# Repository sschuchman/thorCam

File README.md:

# Thoracic Camera

## Overview
The **Thoracic Camera** project is a collaborative effort to design a dynamic thoracic camera system capable of precision actuation and real-time feedback for use in minimally invasive surgeries. By combining a Raspberry Pi 5 for advanced processing and a Raspberry Pi Pico for motor control and sensor feedback, the system delivers a robust solution for camera tracking and actuation in the chest cavity.

---

## Contributors
- **Sean Schuchman**: January 2024 - December 2024  
- **Jakob Schoeberle**: August 2024 - December 2024  
- **Colton Wall**: August 2024 - December 2024  

---

## Hardware

### Raspberry Pi 5
- **Role**: Central processing hub for the system.  
- **Responsibilities**:
  - Handles video feed from the Pi Camera Module V3.
  - Performs computer vision tasks to detect and track a target object.
  - Sends actuation commands to the Pico Controller via UART.

### Pico Controller (Raspberry Pi Pico)
- **Role**: Camera actuation controller.  
- **Responsibilities**:
  - Interprets movement commands from the Raspberry Pi 5 and drives stepper motors.
  - Monitors sensor feedback from tension modules to ensure proper wire tension.
  - Handles precise actuation of the thoracic camera in response to commands.

---

## Pico Controller
The **Pico Controller** acts as an abstraction layer between the computer vision system on the Raspberry Pi 5 and the physical camera actuation system. It simplifies control by encapsulating motor and tension management, providing an easy-to-interface control system.  

### Features:
- **Camera Actuation**:  
  Controls stepper motors to manipulate tension wires, enabling the camera to move along the x-plane and y-plane directions.  
- **Tension Monitoring**:  
  Uses sensor feedback from load cells to dynamically adjust wires and maintain system balance.  
- **Control Modes**:  
  - **Manual Mode**: Direct input to move the camera.  
  - **Automatic Mode**: Actuation based on computer vision commands from the Raspberry Pi 5.  

---

## Directory Structure
The project is divided into several directories to organize hardware, software, and firmware resources.

- `/Software`: Contains software running on the Raspberry Pi 5, including computer vision and the Flask web application for control.  
- `/Firmware`: Firmware for the Raspberry Pi Pico to manage motor control and tension monitoring.  
- `/Hardware`: Schematic diagrams, PCB designs, and other hardware resources.  
- `/Datasheets`: Documentation for components such as stepper motors, motor drivers, and sensors.  
- `/3D_Models`: 3D printable designs for physical components.  
- `/legacy`: Archive of previous iterations or deprecated designs.

---

## Setup

### Raspberry Pi Pico Setup
1. **Development Environment**:
   - Use Visual Studio Code with the Raspberry Pi Pico extension to build and flash the firmware.
   - Ensure the Raspberry Pi Pico Debug Probe is connected for flashing and debugging.  

2. **Firmware Installation**:
   - Clone the repository and navigate to the `/Firmware` directory.
   - Open the project in Visual Studio Code and use the Pico extension to compile and flash the firmware.  

3. **Hardware Connections**:
   - Connect stepper motors via L293D drivers to the GPIO pins.
   - Connect ADS1115 ADC modules to GPIO4 (SDA) and GPIO5 (SCL).
   - Ensure UART pins (GPIO0 and GPIO1) are connected to the Raspberry Pi 5 for communication.

### Raspberry Pi 5 Setup
1. **Install Required Software**:
   - Ensure Python is installed with the required libraries (`Flask`, `OpenCV`, etc.).
   - Navigate to the `/Software` directory and install dependencies using:
     ```bash
     pip install -r requirements.txt
     ```

2. **Start the Web Application**:
   - Run the `app.py` script to start the Flask web server:
     ```bash
     python app.py
     ```
   - Access the control interface via a web browser on the local network.

3. **Hardware Connections**:
   - Connect the Pi Camera Module V3 to the CSI port.
   - Ensure UART is configured on `/dev/ttyAMA0` for communication with the Pico Controller.

---

## Usage
1. **Manual Control**:
   - Use the web interface to manually send movement commands to the Pico Controller.
   - Adjust camera settings and monitor sensor feedback through the interface.

2. **Automatic Control**:
   - Enable automatic mode via the web interface to allow the system to track a selected object.
   - The Raspberry Pi 5 processes the video feed to calculate the offset and sends movement commands to the Pico Controller.

3. **Real-Time Feedback**:
   - Monitor sensor values and system logs in the web interface.
   - View live video and mask feeds to verify object tracking.

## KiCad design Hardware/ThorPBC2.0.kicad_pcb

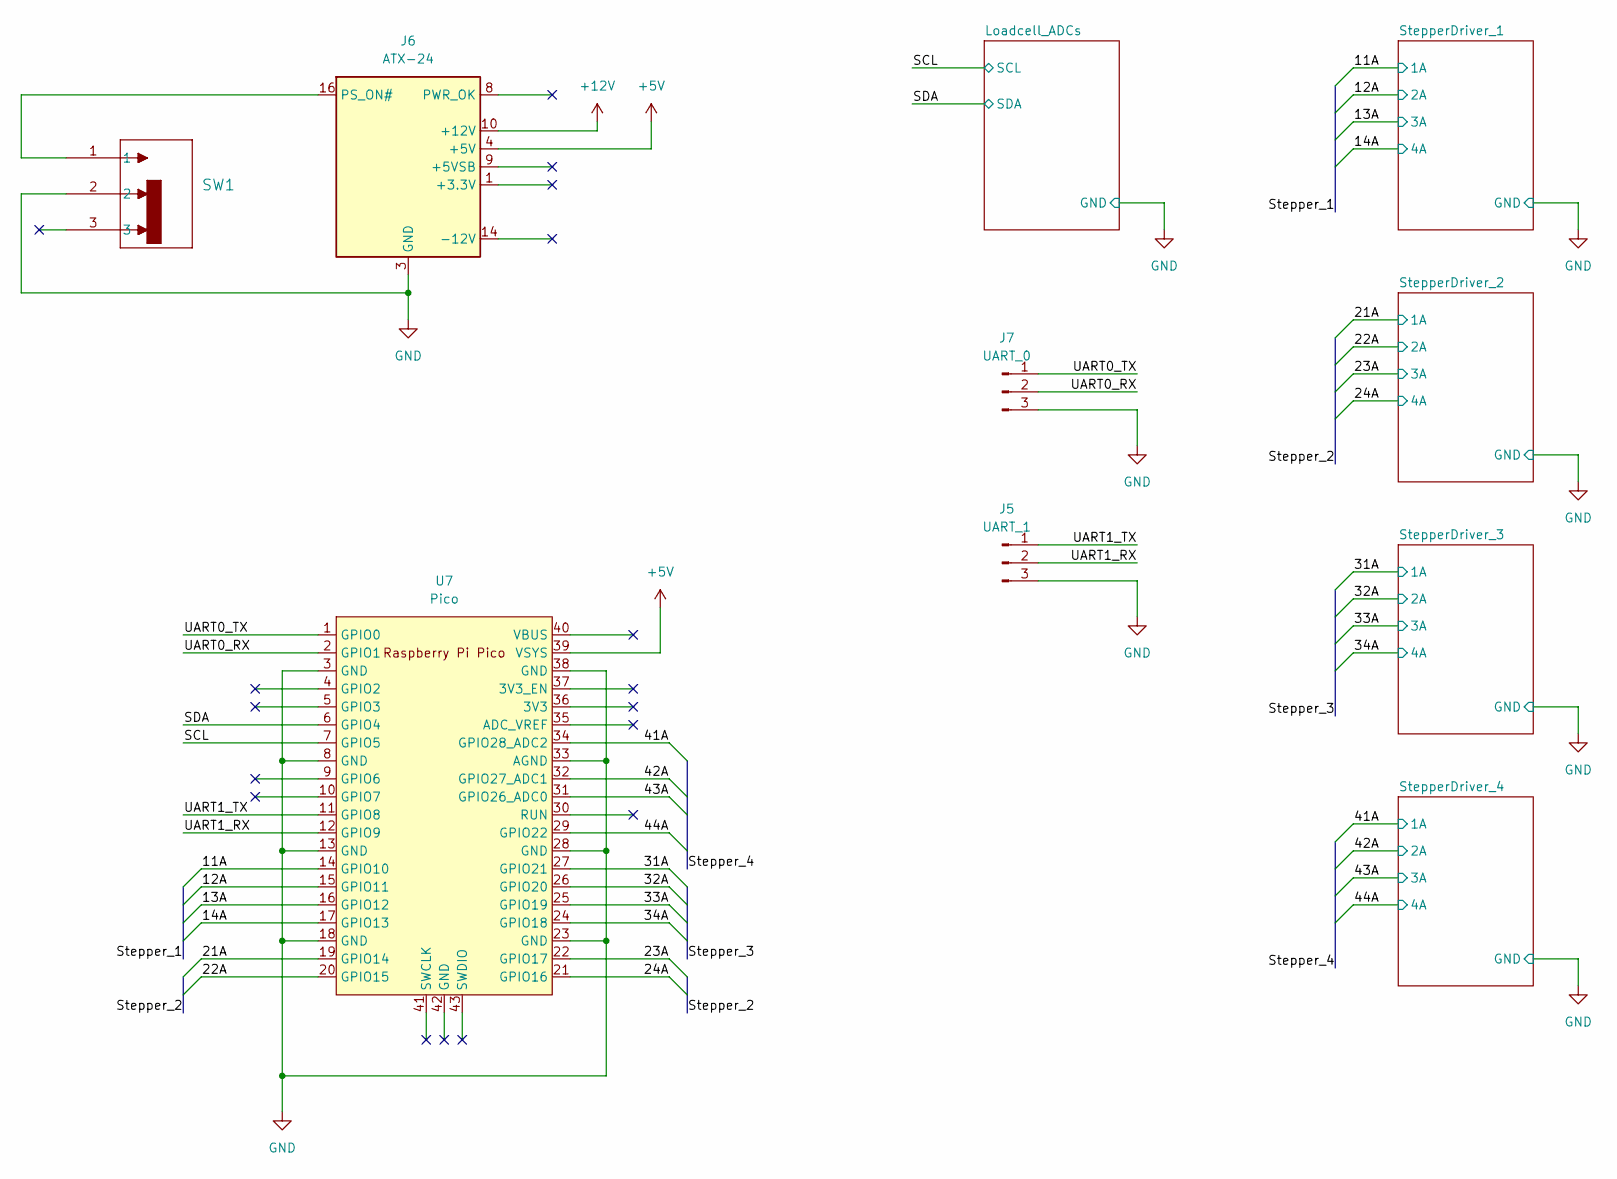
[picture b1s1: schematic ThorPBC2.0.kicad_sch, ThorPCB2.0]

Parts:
J5: UART_1; PinHeader_1x03_P2.54mm_Vertical
J6: ATX-24; Molex_Mini-Fit_Jr_5566-24A_2x12_P4.20mm_Vertical_Thor
J7: UART_0; PinHeader_1x03_P2.54mm_Vertical
SW1: OS102011MS2QN1; SPDT_OS102011_CNK
U7: Pico; RPi_Pico_SMD_TH

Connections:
+5V: J6.4 (+5V), J6.6 (+5V), J6.21 (+5V), J6.22 (+5V), J6.23 (+5V), U7.39 (VSYS); also elsewhere on the board
+12V: J6.10 (+12V), J6.11 (+12V); also elsewhere on the board
/11A: U7.14 (GPIO10); also elsewhere on the board
/12A: U7.15 (GPIO11); also elsewhere on the board
/13A: U7.16 (GPIO12); also elsewhere on the board
/14A: U7.17 (GPIO13); also elsewhere on the board
/21A: U7.19 (GPIO14); also elsewhere on the board
/22A: U7.20 (GPIO15); also elsewhere on the board
/23A: U7.22 (GPIO17); also elsewhere on the board
/24A: U7.21 (GPIO16); also elsewhere on the board
/31A: U7.27 (GPIO21); also elsewhere on the board
/32A: U7.26 (GPIO20); also elsewhere on the board
/33A: U7.25 (GPIO19); also elsewhere on the board
/34A: U7.24 (GPIO18); also elsewhere on the board
/41A: U7.34 (GPIO28_ADC2); also elsewhere on the board
/42A: U7.32 (GPIO27_ADC1); also elsewhere on the board
/43A: U7.31 (GPIO26_ADC0); also elsewhere on the board
/44A: U7.29 (GPIO22); also elsewhere on the board
/SCL: U7.7 (GPIO5); also elsewhere on the board
/SDA: U7.6 (GPIO4); also elsewhere on the board
/UART0_RX: J7.2, U7.2 (GPIO1)
/UART0_TX: J7.1, U7.1 (GPIO0)
/UART1_RX: J5.2, U7.12 (GPIO9)
/UART1_TX: J5.1, U7.11 (GPIO8)
GND: J5.3, J6.3 (GND), J6.5 (GND), J6.7 (GND), J6.15 (GND), J6.17 (GND), J6.18 (GND), J6.19 (GND), J6.24 (GND), J7.3, SW1.2, U7.3 (GND), U7.8 (GND), U7.13 (GND), U7.18 (GND), U7.23 (GND), U7.28 (GND), U7.33 (AGND), U7.38 (GND); also elsewhere on the board
unnamed: J6.16 (PS_ON#), SW1.1

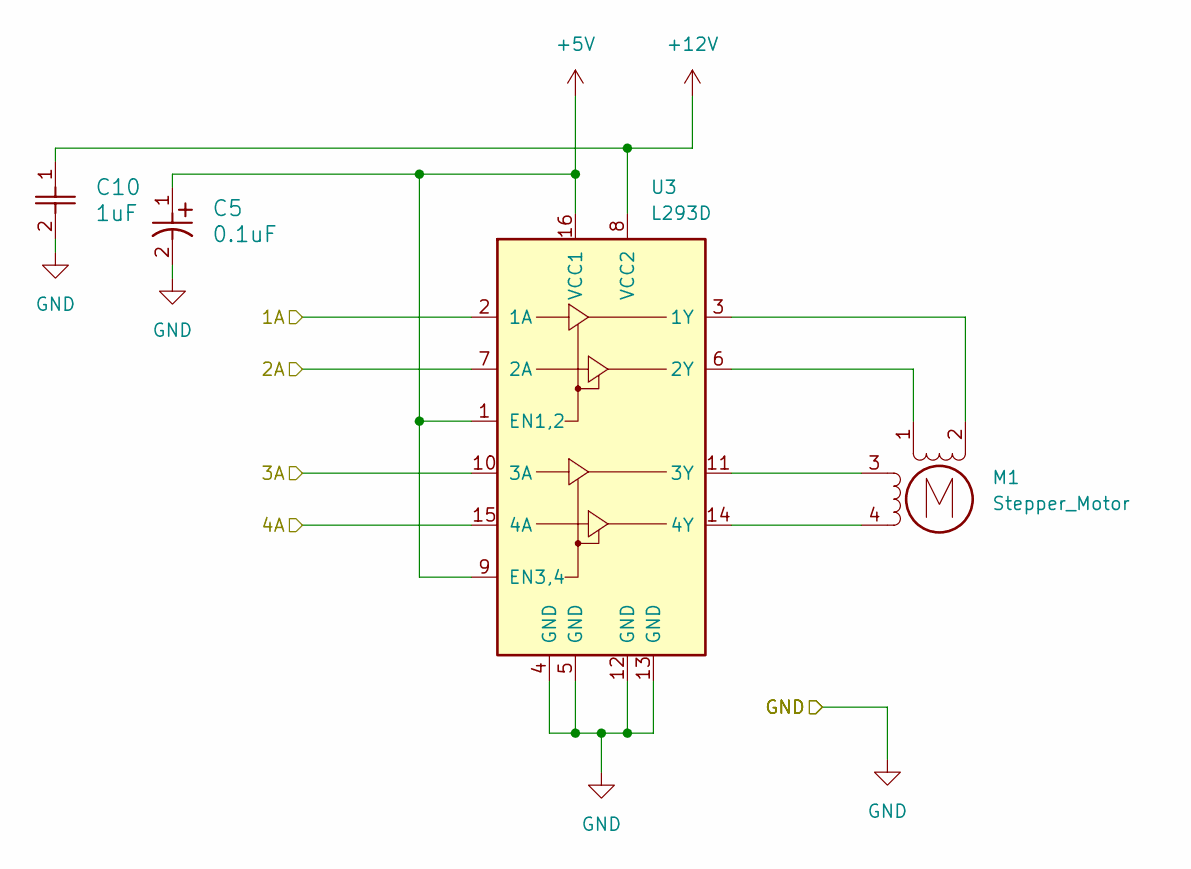
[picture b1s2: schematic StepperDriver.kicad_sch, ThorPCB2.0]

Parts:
C5: 0.1uF; CAP_C320_KEM
C10: 1uF; CAP_C330C_MR_X7R_KEM
M1: Stepper_Motor; TerminalBlock_Phoenix_MPT-0,5-4-2.54_1x04_P2.54mm_Horizontal
U3: L293D; DIP-16_W7.62mm

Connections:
+5V: C5.1, U3.1 (EN1,2), U3.9 (EN3,4), U3.16 (VCC1); also elsewhere on the board
+12V: C10.1, U3.8 (VCC2); also elsewhere on the board
/11A: U3.2 (1A); also elsewhere on the board
/12A: U3.7 (2A); also elsewhere on the board
/13A: U3.10 (3A); also elsewhere on the board
/14A: U3.15 (4A); also elsewhere on the board
GND: C5.2, C10.2, U3.4 (GND), U3.5 (GND), U3.12 (GND), U3.13 (GND); also elsewhere on the board
unnamed: M1.2 (-), U3.3 (1Y)
unnamed: M1.1, U3.6 (2Y)
unnamed: M1.3, U3.11 (3Y)
unnamed: M1.4, U3.14 (4Y)

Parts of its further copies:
C7, C8, C9: 0.1uF; CAP_C320_KEM
C11, C12, C13: 1uF; CAP_C330C_MR_X7R_KEM
M2, M3, M4: Stepper_Motor; TerminalBlock_Phoenix_MPT-0,5-4-2.54_1x04_P2.54mm_Horizontal
U4, U5, U6: L293D; DIP-16_W7.62mm

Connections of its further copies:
+5V: C7.1, C8.1, C9.1, U4.1 (EN1,2), U4.9 (EN3,4), U4.16 (VCC1), U5.1 (EN1,2), U5.9 (EN3,4), U5.16 (VCC1), U6.1 (EN1,2), U6.9 (EN3,4), U6.16 (VCC1); also elsewhere on the board
+12V: C11.1, C12.1, C13.1, U4.8 (VCC2), U5.8 (VCC2), U6.8 (VCC2); also elsewhere on the board
/21A: U4.2 (1A); also elsewhere on the board
/22A: U4.7 (2A); also elsewhere on the board
/23A: U4.10 (3A); also elsewhere on the board
/24A: U4.15 (4A); also elsewhere on the board
/31A: U5.2 (1A); also elsewhere on the board
/32A: U5.7 (2A); also elsewhere on the board
/33A: U5.10 (3A); also elsewhere on the board
/34A: U5.15 (4A); also elsewhere on the board
/41A: U6.2 (1A); also elsewhere on the board
/42A: U6.7 (2A); also elsewhere on the board
/43A: U6.10 (3A); also elsewhere on the board
/44A: U6.15 (4A); also elsewhere on the board
GND: C7.2, C8.2, C9.2, C11.2, C12.2, C13.2, U4.4 (GND), U4.5 (GND), U4.12 (GND), U4.13 (GND), U5.4 (GND), U5.5 (GND), U5.12 (GND), U5.13 (GND), U6.4 (GND), U6.5 (GND), U6.12 (GND), U6.13 (GND); also elsewhere on the board
unnamed: M2.2 (-), U4.3 (1Y)
unnamed: M3.2 (-), U5.3 (1Y)
unnamed: M4.2 (-), U6.3 (1Y)
unnamed: M2.1, U4.6 (2Y)
unnamed: M2.3, U4.11 (3Y)
unnamed: M2.4, U4.14 (4Y)
unnamed: M3.1, U5.6 (2Y)
unnamed: M3.3, U5.11 (3Y)
unnamed: M3.4, U5.14 (4Y)
unnamed: M4.1, U6.6 (2Y)
unnamed: M4.3, U6.11 (3Y)
unnamed: M4.4, U6.14 (4Y)

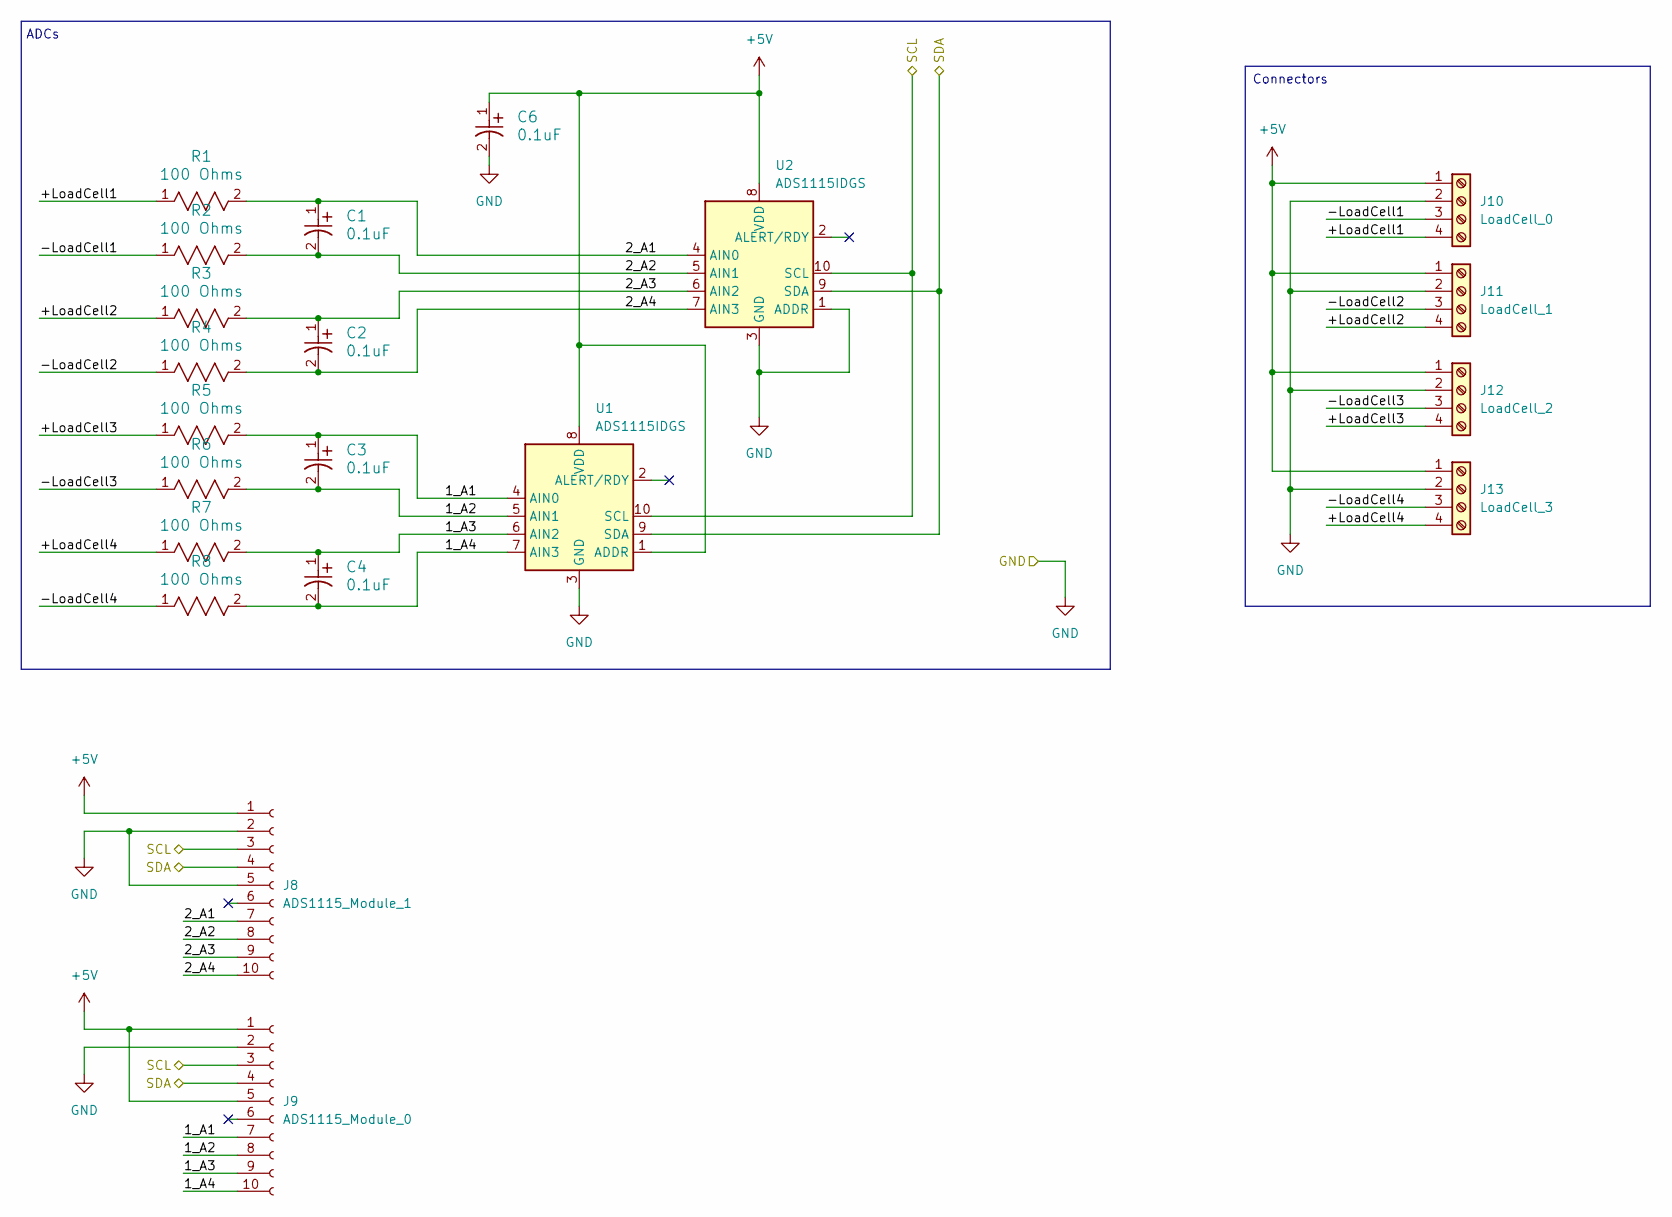
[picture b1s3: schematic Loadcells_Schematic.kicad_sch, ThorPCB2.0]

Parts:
C1, C2, C3, C4, C6: 0.1uF; CAP_C320_KEM
J8: ADS1115_Module_1; ADS1115_1x10_P2.54mm_Vertical
J9: ADS1115_Module_0; ADS1115_1x10_P2.54mm_Vertical
J10: LoadCell_0; TerminalBlock_Phoenix_MPT-0,5-4-2.54_1x04_P2.54mm_Horizontal
J11: LoadCell_1; TerminalBlock_Phoenix_MPT-0,5-4-2.54_1x04_P2.54mm_Horizontal
J12: LoadCell_2; TerminalBlock_Phoenix_MPT-0,5-4-2.54_1x04_P2.54mm_Horizontal
J13: LoadCell_3; TerminalBlock_Phoenix_MPT-0,5-4-2.54_1x04_P2.54mm_Horizontal
R1, R2, R3, R4, R5, R6, R7, R8: 100 Ohms; RES_TYCO_YR1_TYC
U1, U2: ADS1115IDGS; TSSOP-10_3x3mm_P0.5mm

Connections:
+5V: C6.1, J8.1, J9.1, J9.5, J10.1, J11.1, J12.1, J13.1, U1.1 (ADDR), U1.8 (VDD), U2.8 (VDD); also elsewhere on the board
/Loadcell_ADCs/1_A1: C3.1, J9.7, R5.2, U1.4 (AIN0)
/Loadcell_ADCs/1_A2: C3.2, J9.8, R6.2, U1.5 (AIN1)
/Loadcell_ADCs/1_A3: C4.1, J9.9, R7.2, U1.6 (AIN2)
/Loadcell_ADCs/1_A4: C4.2, J9.10, R8.2, U1.7 (AIN3)
/Loadcell_ADCs/2_A1: C1.1, J8.7, R1.2, U2.4 (AIN0)
/Loadcell_ADCs/2_A2: C1.2, J8.8, R2.2, U2.5 (AIN1)
/Loadcell_ADCs/2_A3: C2.1, J8.9, R3.2, U2.6 (AIN2)
/Loadcell_ADCs/2_A4: C2.2, J8.10, R4.2, U2.7 (AIN3)
/Loadcell_ADCs/+LoadCell1: J10.4, R1.1
/Loadcell_ADCs/+LoadCell2: J11.4, R3.1
/Loadcell_ADCs/+LoadCell3: J12.4, R5.1
/Loadcell_ADCs/+LoadCell4: J13.4, R7.1
/Loadcell_ADCs/-LoadCell1: J10.3, R2.1
/Loadcell_ADCs/-LoadCell2: J11.3, R4.1
/Loadcell_ADCs/-LoadCell3: J12.3, R6.1
/Loadcell_ADCs/-LoadCell4: J13.3, R8.1
/SCL: J8.3, J9.3, U1.10 (SCL), U2.10 (SCL); also elsewhere on the board
/SDA: J8.4, J9.4, U1.9 (SDA), U2.9 (SDA); also elsewhere on the board
GND: C6.2, J8.2, J8.5, J9.2, J10.2, J11.2, J12.2, J13.2, U1.3 (GND), U2.1 (ADDR), U2.3 (GND); also elsewhere on the board

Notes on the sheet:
ADCs
Connectors

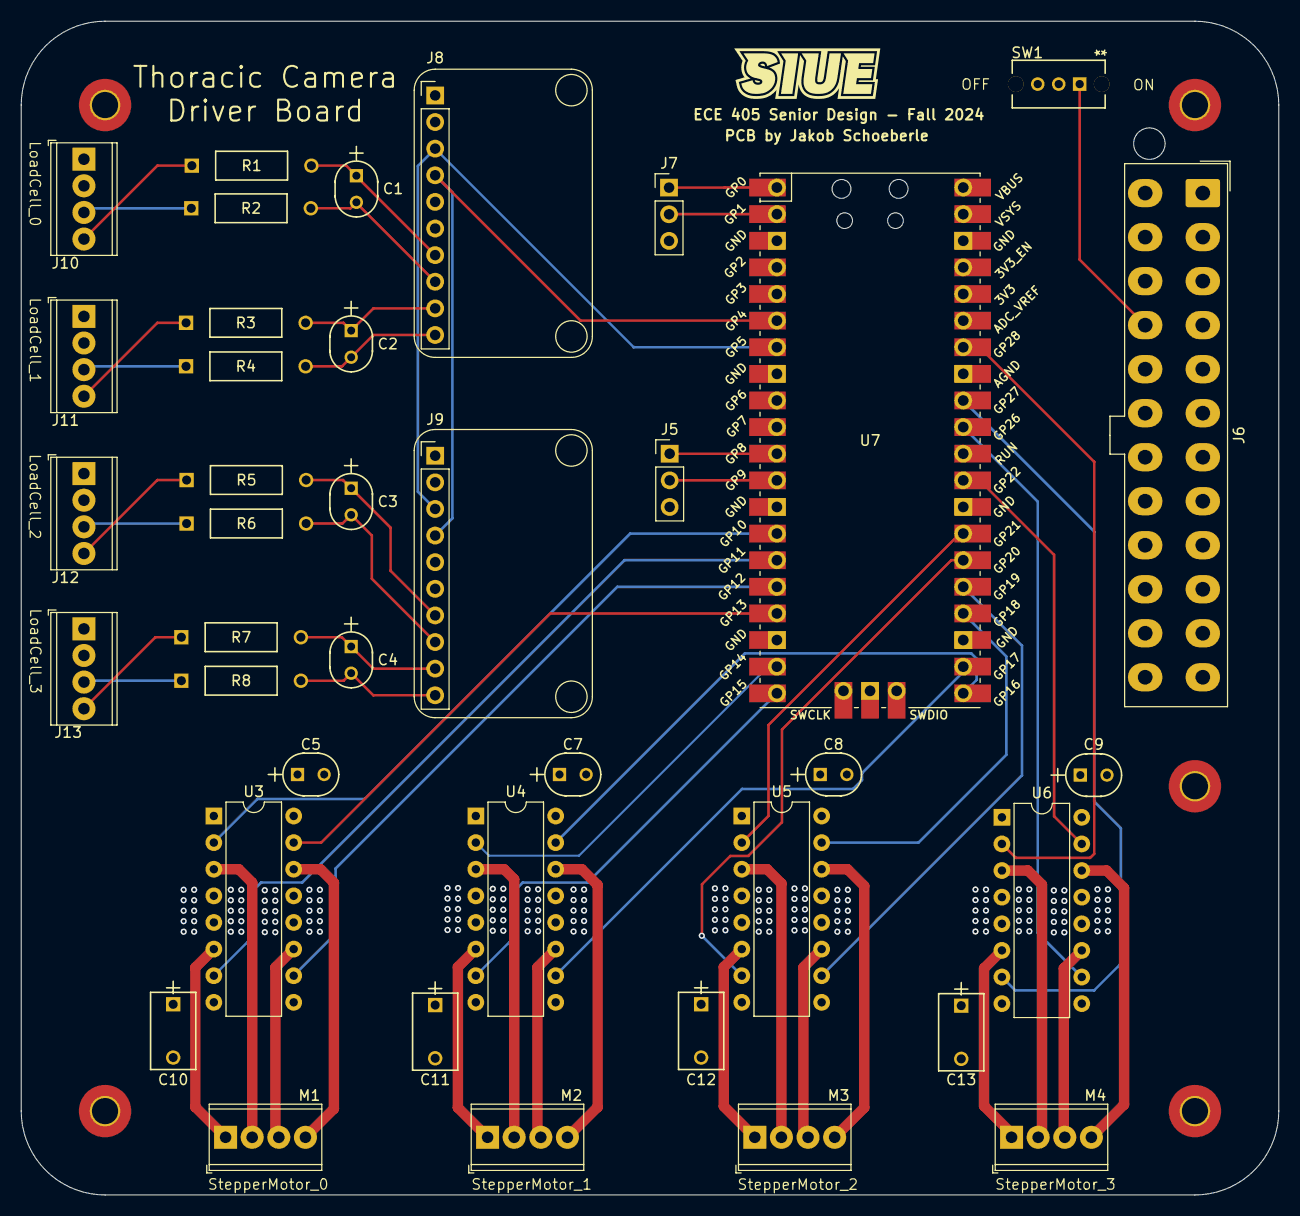
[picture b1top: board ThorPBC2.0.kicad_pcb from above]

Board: 4 copper layers, 120.0 x 112.0 mm, 39 parts (0 on the bottom side), 58 nets.

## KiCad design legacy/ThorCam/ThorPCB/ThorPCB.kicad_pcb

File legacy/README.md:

# ThorCam
## URCA

# Contributors
Sean Schuchman: January 2024 - July 2024

# Setup

# Push to Remote
*** git push [URL] will not work:
```
git init
git add .
git commit -m "<insert comment here>"
git push --set-upstream origin --all
```

# Project Hierarchy
- Raspberry Pi 4
    - Handle camera module video feed
    - Computer vision to determine location of target
    - Send input to Pico Controller to handle actuation of camera in desired direction

- Pico Controller
    - Takes in input of direction to drive the camera actuation
    - Takes in sensor data from tension modules to maintain proper control wire tension
    - Drives stepper motors for tension wire control

- Tension Module
    - Reads control wire tension via pressure sensor
    - Analog signal fed through Op-Amp buffer to ADC module
    - ACD module connected to I2C bus
    - Four tension modules for each control wire are connected along Pico Controller I2C bus by the ACD module I2C interface
    - Tension module provides analog data on pressure sensor, as well as target tension by means of analog voltage

# Pico Controller
The Pico Controller is designed to serve as the abstraction layer between the computer vision element and the camera actuation control. This is intended to simplify the project by containerizing the physical movement and control of the camera into a simple to interface.

The Pico Controller is configured to handle camera actuation by control of the stepper motor wires, as well as receive data from the tension modules to adjust the control wires to maintain proper balance.

The Pico Controller can be controlled manually or via remote software driver with simple controls to actuate the camera in any combination of x-plane or y-plane directions.

Project files can be found under the project directory:
/dev/pico_controller

## Hardware
- Raspberry Pi Pico
    - RP2040 microcontroller chip
    - Dual-core ARM Cortex M0+ processor, clock up to 133 MHz
    - 264kB SRAM, 2MB on-board flash memory

## Dev Environment
- Raspberry Pi 4
    - Thonny IDE
    - MircoPython SDK for Pi Pico

## Raspberry Pi Pico Setup
Follow steps in YouTube tutorial for setup:
https://www.youtube.com/watch?v=Zy64kZEM_bg

1. Connect Pi Pico to Raspberry Pi 4 (or alternative version) via USB. Be sure to hold down reset button on Pi Pico while connecting to enable bootloader mode.
2. Access Pi Pico as a directory in file explorer.
3. Copy the MicroPython library 'RPI_PICO-20240105-v1.22.1.uf2' to the Pi Pico. MicroPython UF2 library file can be found in project directory: /dev/pico_controller.
4. Pi Pico should be ready to target as available device in Thonny IDE.

More information can be found at Raspberry Pi Pico Docs:
https://www.raspberrypi.com/documentation/microcontrollers/micropython.html

- Download the latest UF2 file from this page. Found under "Download the correct MicroPython UF2 file for your board:" and select the appropriate device.

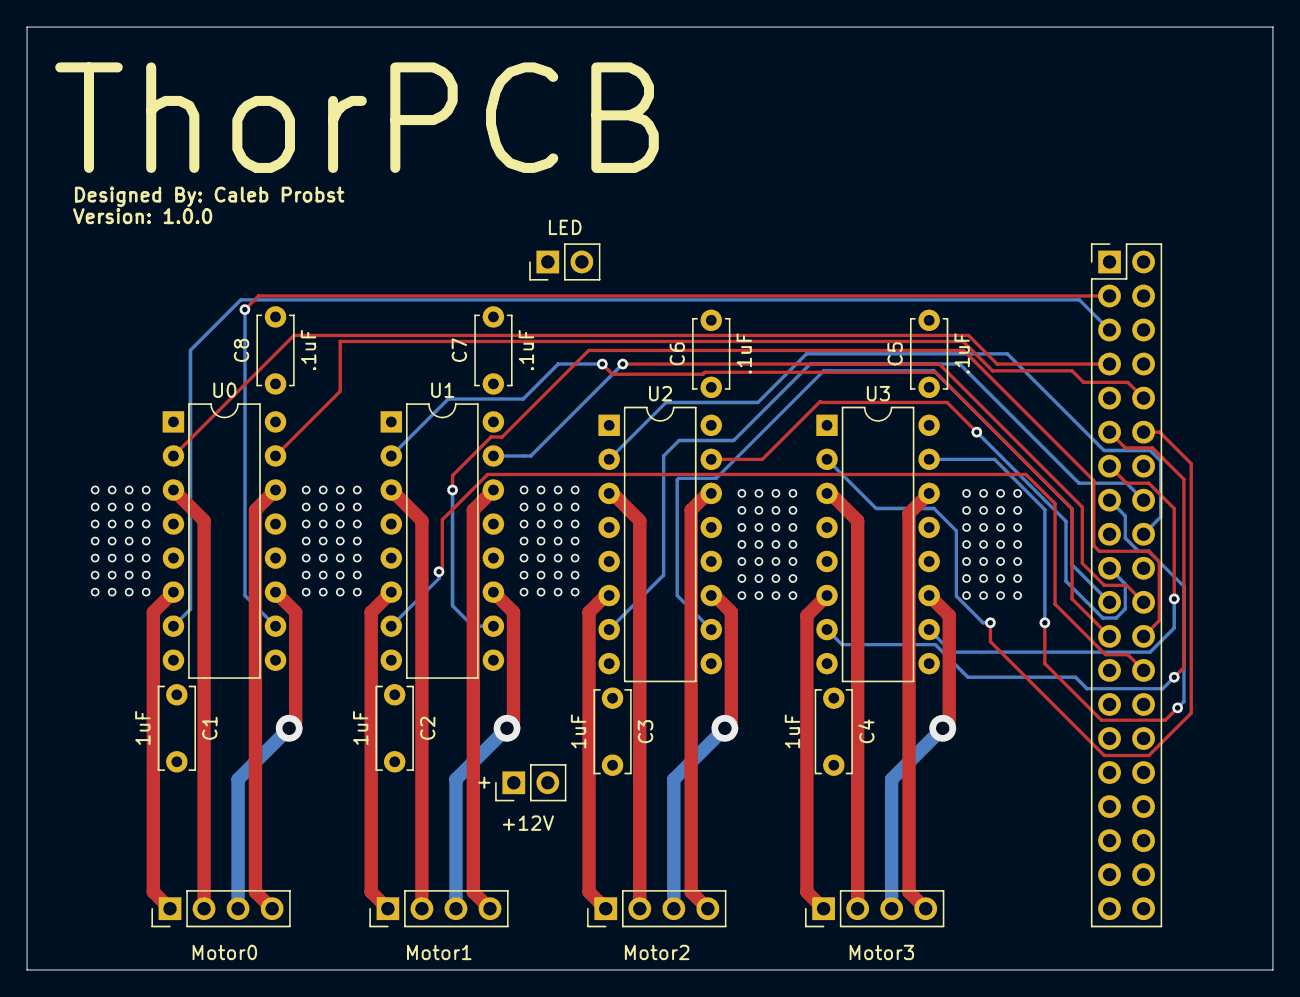
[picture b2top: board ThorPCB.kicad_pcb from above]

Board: 4 copper layers, 93.0 x 70.4 mm, 19 parts (0 on the bottom side), 35 nets.

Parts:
+: +12V; PinHeader_1x02_P2.54mm_Vertical
C1, C2, C3, C4: 1uF; C_Disc_D6.0mm_W2.5mm_P5.00mm
C5, C6, C7, C8: .1uF; C_Disc_D5.0mm_W2.5mm_P5.00mm
J1: RaspPiHeader; PinHeader_2x20_P2.54mm_Vertical
J3: LED; PinHeader_1x02_P2.54mm_Vertical
M0: Motor0; PinHeader_1x04_P2.54mm_Vertical
M1: Motor1; PinHeader_1x04_P2.54mm_Vertical
M2: Motor2; PinHeader_1x04_P2.54mm_Vertical
M3: Motor3; PinHeader_1x04_P2.54mm_Vertical
U0, U1, U2, U3: L293D; DIP-16_W7.62mm

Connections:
+5V: C5.1, C6.1, C7.1, C8.1, J1.2, J1.4, J3.1, U0.1 (EN1,2), U0.9 (EN3,4), U0.16 (VCC1), U1.1 (EN1,2), U1.9 (EN3,4), U1.16 (VCC1), U2.1 (EN1,2), U2.9 (EN3,4), U2.16 (VCC1), U3.1 (EN1,2), U3.9 (EN3,4), U3.16 (VCC1)
+12V: +.1, C1.1, C2.1, C3.1, C4.1, U0.8 (VCC2), U1.8 (VCC2), U2.8 (VCC2), U3.8 (VCC2)
GND: +.2, C1.2, C2.2, C3.2, C4.2, C5.2, C6.2, C7.2, C8.2, J1.6, J1.9, J1.14, J1.20, J1.25, J1.30, J1.34, J1.39, J3.2, U0.4 (GND), U0.5 (GND), U0.12 (GND), U0.13 (GND), U1.4 (GND), U1.5 (GND), U1.12 (GND), U1.13 (GND), U2.4 (GND), U2.5 (GND), U2.12 (GND), U2.13 (GND), U3.4 (GND), U3.5 (GND), U3.12 (GND), U3.13 (GND)
unnamed: J1.3, U0.10 (3A)
unnamed: J1.5, U0.7 (2A)
unnamed: J1.7, U0.2 (1A)
unnamed: J1.10, U0.15 (4A)
unnamed: J1.11, U3.7 (2A)
unnamed: J1.12, U3.2 (1A)
unnamed: J1.13, U3.10 (3A)
unnamed: J1.15, U3.15 (4A)
unnamed: J1.16, U2.7 (2A)
unnamed: J1.18, U2.2 (1A)
unnamed: J1.19, U2.15 (4A)
unnamed: J1.21, U2.10 (3A)
unnamed: J1.22, U1.15 (4A)
unnamed: J1.23, U1.2 (1A)
unnamed: J1.24, U1.10 (3A)
unnamed: J1.26, U1.7 (2A)
unnamed: M0.2 (-), U0.3 (1Y)
unnamed: M1.2 (-), U1.3 (1Y)
unnamed: M2.2 (-), U2.3 (1Y)
unnamed: M3.2 (-), U3.3 (1Y)
unnamed: M0.1, U0.6 (2Y)
unnamed: M0.3, U0.11 (3Y)
unnamed: M0.4, U0.14 (4Y)
unnamed: M1.1, U1.6 (2Y)
unnamed: M1.3, U1.11 (3Y)
unnamed: M1.4, U1.14 (4Y)
unnamed: M2.1, U2.6 (2Y)
unnamed: M2.3, U2.11 (3Y)
unnamed: M2.4, U2.14 (4Y)
unnamed: M3.1, U3.6 (2Y)
unnamed: M3.3, U3.11 (3Y)
unnamed: M3.4, U3.14 (4Y)

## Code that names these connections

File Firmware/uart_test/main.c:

#include <stdio.h>
#include "pico/stdlib.h"
#include "hardware/uart.h"

// Define UARTs and pins
#define UART0_ID uart0
#define UART0_TX_PIN 0
#define UART0_RX_PIN 1

#define UART1_ID uart1
#define UART1_TX_PIN 8
#define UART1_RX_PIN 9

int main()
{
    stdio_init_all();

    // Set up UART0 for debug probe
    uart_init(UART0_ID, 115200);
    gpio_set_function(UART0_TX_PIN, GPIO_FUNC_UART);
    gpio_set_function(UART0_RX_PIN, GPIO_FUNC_UART);

    // Set up UART1 for communication with Raspberry Pi
    uart_init(UART1_ID, 115200);
    gpio_set_function(UART1_TX_PIN, GPIO_FUNC_UART);
    gpio_set_function(UART1_RX_PIN, GPIO_FUNC_UART);

    // Send out a string via UART0 (debug probe)
    uart_puts(UART0_ID, "Hello, UART0!\n");

    // Send out a string via UART1 (Raspberry Pi)
    uart_puts(UART1_ID, "Hello, UART1!\n");

    while (true) {
        // Send debug message via UART0
        uart_puts(UART0_ID, "Debug: Hello, world!\n");

        // Send data to Raspberry Pi via UART1
        uart_puts(UART1_ID, "Data: Hello, Raspberry Pi!\n");

        sleep_ms(1000);
    }
}

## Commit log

2024-09-17 Add legacy project files
2024-09-17 Add new dev README.md and fix spelling errors for old one.
2024-09-17 Intial PCB and File Structure Push
2024-09-17 Added git module and added .DS_Store to gitignore
2024-09-17 Added Stuff for pico
2024-09-18 Add current firmware to repo. Included FreeRTOS Kernel repo in project.
2024-09-18 Move README to project root.
2024-09-18 Initialize project directories for software.
2024-09-18 Add hardware datasheets to project.
2024-09-24 Move some files and rename some stuff. Add the 3D model files.
2024-09-24 Add datasheets
2024-09-24 Add images and datasheet
2024-09-24 Add shift register driver.
2024-09-30 Updates to PCB
2024-09-30 Updates to Sch
2024-10-07 Working firmware, calibration, and balancing. Not currently utilizing the FreeRTOS Kernel.
2024-10-07 Add baseline web application. Successful camera feed and UART connection.
2024-10-08 PCB Updates
2024-10-08 Push latest software for thor controller. Has working object tracking, live video feed, analysis mask feed, uart feed, and hue controls.
2024-10-08 Remove old code
2024-10-24 Updated UI for software controller. Added bar graph for live sensor values.
2024-10-24 PCB "Done"
2024-10-24 ATX24 was not right
2024-10-29 Added Back Silkscreen image
2024-10-30 Final Updates
2024-10-30 Got rid of old files
2024-10-30 Power and GND plane fixed
2024-10-31 Added bar chart.
2024-11-01 Production PCB Version
2024-11-26 Update UI for live bar chart sensor values, target color sliders.
2024-11-26 Add direction movement for camera. Adjust threshold values.
2024-11-29 Pico can get commands via uart. Break out the sensor and movement functions from main.c into helper files.
2024-11-29 Reorganize src and include files
2024-11-29 Create core1 task list in main.c. Core0 task runs within infinite loop at end of main.
2024-12-01 Calibrated movement controls from thor-controller via UART.
2024-12-01 Add manual and automatic control toggle
2024-12-02 Change UI for dark mode. Swap X sign for correct object tracking direction.
2024-12-03 Remove unused README
2024-12-05 Remove unnecessary README
2024-12-05 Add logo image
2024-12-05 Update UI to minimal design, clean up code
2024-12-05 Comment out SPF counter, and adjust FPS placement
2024-12-05 working updated UI. Clean up code
2024-12-06 Update UI. Create demo mode. Add threshold lines in bar graph.
2024-12-06 Added the correct color
2024-12-10 Add first draft of LaTeX report.
2024-12-10 Remove unnecessary files.
2024-12-10 Edit report, format the video link to make it more obvious.
2024-12-12 Added .vscode to hide latex junk
2024-12-12 Added to the Bill of Materials
2024-12-12 Update BOM totals
2024-12-13 Added Images
2024-12-13 Added figures into text
2024-12-13 Final revision.
